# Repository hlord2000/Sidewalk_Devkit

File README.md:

# Sidewalk Devkit

KiCad hardware design for a compact Nordic Semiconductor devkit built around an
`nRF54L15` target, `nPM1300` power management, and an `SX1262` sub-GHz radio
front end.

## Hardware

- `nRF54L15-QFAA` target SoC with external `32 MHz` and `32.768 kHz` crystals.
- `nPM1300-QEAA` PMIC for USB/battery power management, charging, and status LEDs.
- `SX1262IMLTRT` sub-GHz transceiver with RF switch/filter network, U.FL, and chip antenna footprints.
- On-board `nRF52833-QDXX` debug helper with USB, SWD, UART, and level-translated target boundary.
- USB-C input with ESD protection and a 1 A fuse.
- Battery connector, reset/user buttons, and board-edge debug/test access.
- `STEMMA QT` I2C expansion connector.
- `SHT4x` humidity/temperature sensor, `ADXL367` accelerometer, and `ZD25WQ16CEIGR` QSPI flash.
- NFC connector footprint and user/status LEDs.

## Board

| Property | Value |
| --- | --- |
| KiCad version | 10.x project files |
| Board revision | `0.1` |
| Size | `55 mm x 34 mm` |
| Stackup | 6 copper layers, 1.6 mm board thickness |
| Minimum track / clearance | `0.127 mm / 0.127 mm` |
| Minimum drill | `0.200 mm` |

## Passed Qualification Tests

- Flashing the `nRF54L15` target from the on-board `nRF52833` debug helper.
- RTT logging.
- UART logging.
- BLE validation.
- NFC validation.
- Sensor and PMIC logging from `SHT40`, `ADXL367`, and `nPM1300`.
- `SX1262` radio operation in both FSK and LoRa modes.
- Sidewalk operation over all transports.

### Top

### Bottom

## Schematic Structure

The design is split into hierarchical KiCad sheets:

- `sch/nRF54L15.kicad_sch` - target SoC, sensors, QSPI flash, STEMMA QT, NFC, and user IO.
- `sch/SX1262.kicad_sch` - sub-GHz radio, RF matching/filtering, antenna switch, and RF connectors.
- `sch/nPM1300.kicad_sch` - USB-C, battery input, PMIC rails, charger support, and PMIC LEDs.
- `sch/Debugger.kicad_sch` - on-board debug helper, target SWD/UART boundary, and level shifting.

## Repository Layout

```text
.
|-- Sidewalk_Devkit.kicad_pro   KiCad project
|-- Sidewalk_Devkit.kicad_sch   Top-level schematic
|-- Sidewalk_Devkit.kicad_pcb   PCB layout
|-- sch/                        Hierarchical schematic sheets
|-- lib/                        Local symbols, footprints, and 3D models
|-- docs/images/                README render images
|-- build/                      Local generated outputs, ignored by git
`-- debug_helper_parts.md       Notes for the debug-helper boundary parts
```

## Regenerating Outputs

The README images are rendered directly from the KiCad PCB:

```bash
mkdir -p docs/images

kicad-cli pcb render Sidewalk_Devkit.kicad_pcb \
  --output docs/images/sidewalk-devkit-hero.png \
  --width 1800 --height 1000 \
  --background opaque --quality high --perspective \
  --rotate '-35,0,35' --zoom 0.84

kicad-cli pcb render Sidewalk_Devkit.kicad_pcb \
  --output docs/images/sidewalk-devkit-top.png \
  --width 1600 --height 900 \
  --side top --background opaque --quality high --zoom 1.12

kicad-cli pcb render Sidewalk_Devkit.kicad_pcb \
  --output docs/images/sidewalk-devkit-bottom.png \
  --width 1600 --height 900 \
  --side bottom --background opaque --quality high --zoom 1.12
```

Useful local exports:

```bash
mkdir -p build

kicad-cli sch export pdf Sidewalk_Devkit.kicad_sch \
  --output build/schematic.pdf

kicad-cli pcb export step Sidewalk_Devkit.kicad_pcb \
  --output build/board.step

kicad-cli sch export bom Sidewalk_Devkit.kicad_sch \
  --output build/bom.csv \
  --fields Reference,Value,Footprint,QUANTITY,DNP \
  --group-by Value,Footprint
```

The custom EasyEDA-derived footprints and 3D models live under `lib/`. STEP
export may still warn if a local KiCad installation does not include every
referenced stock KiCad 3D model.

Run design checks before fabrication or release:

```bash
mkdir -p build
kicad-cli sch erc Sidewalk_Devkit.kicad_sch --output build/erc.rpt
kicad-cli pcb drc Sidewalk_Devkit.kicad_pcb --output build/drc.rpt
```

## License

This hardware design is licensed under the CERN Open Hardware Licence Version 2
- Permissive. See [LICENSE](LICENSE).

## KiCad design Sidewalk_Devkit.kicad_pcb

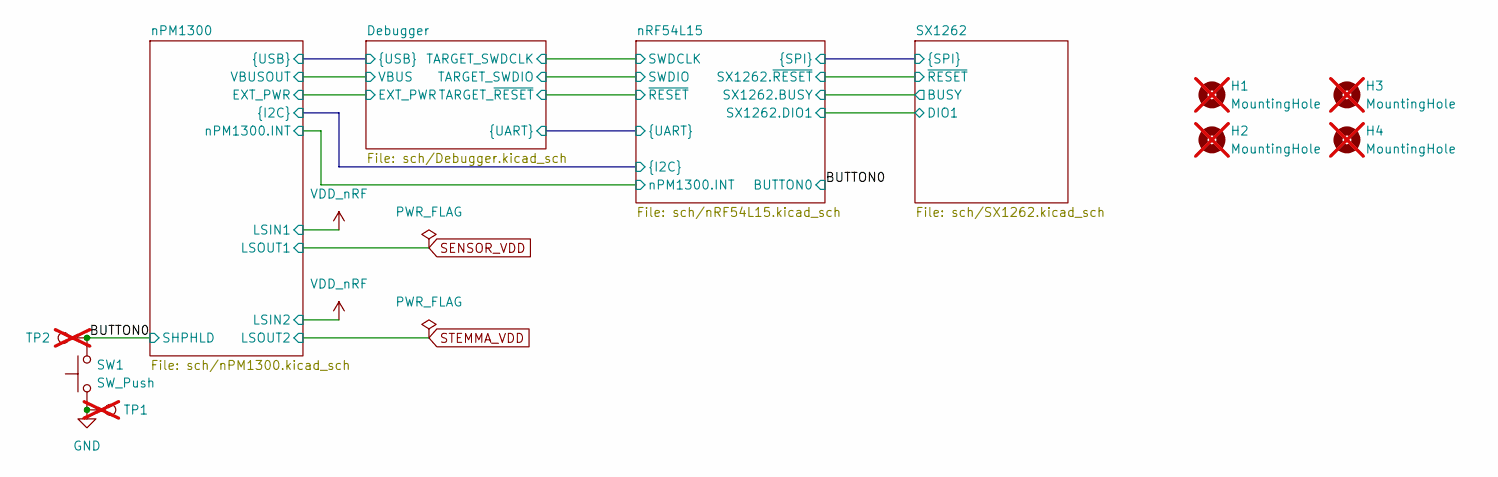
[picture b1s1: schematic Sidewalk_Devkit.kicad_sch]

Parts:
H1, H2, H3, H4: MountingHole; MountingHole_2.2mm_M2; not fitted
SW1: SW_Push; SW_Push_1P1T_NO_Vertical_Wuerth_434133025816; LCSC C127488
TP1: TestPoint; TestPoint_Keystone_5015_Micro_Mini; not fitted
TP2: TestPoint; TestPoint_Pad_D1.0mm; not fitted

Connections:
/BUTTON0: SW1.2, TP2.1 (1_1); also elsewhere on the board
GND: SW1.1, TP1.1 (1_1); also elsewhere on the board

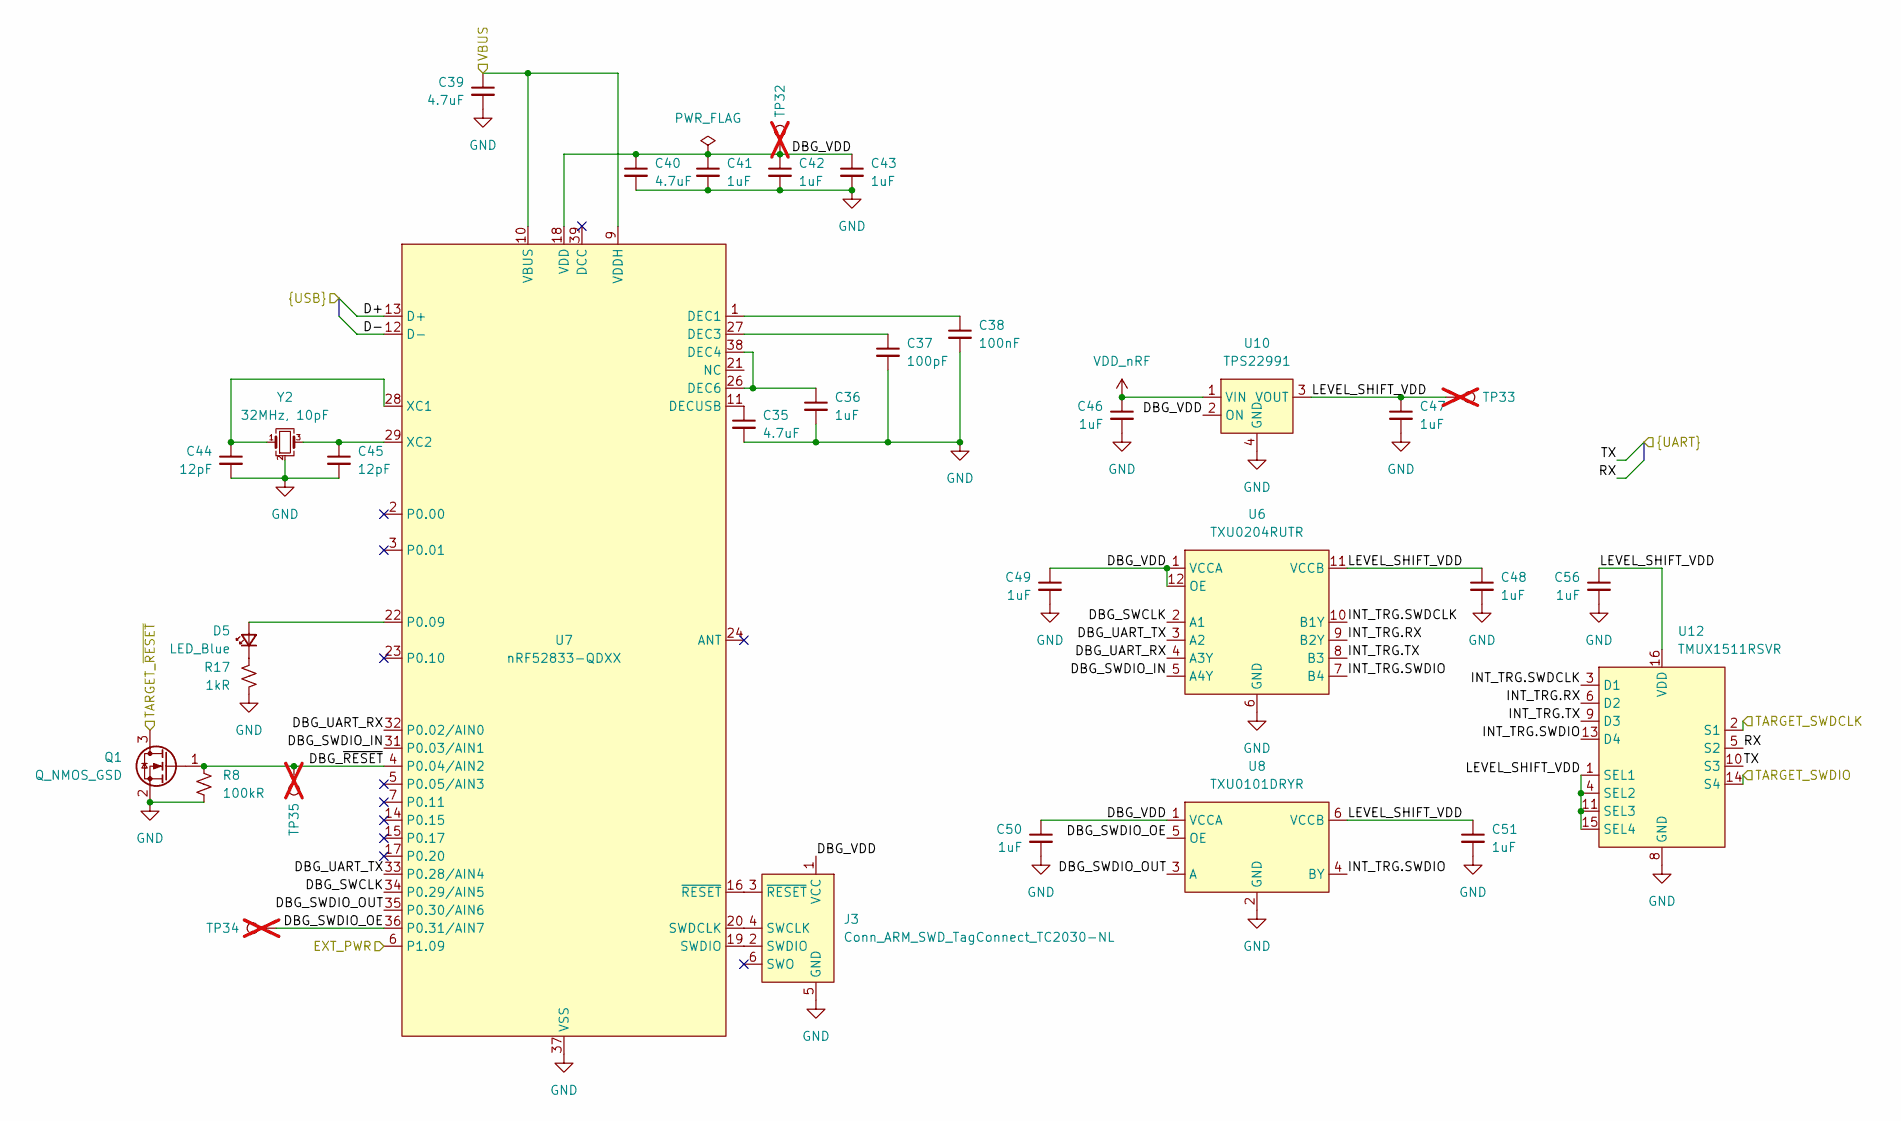
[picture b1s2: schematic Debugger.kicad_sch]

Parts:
C35, C40: 4.7uF; C_0201_0603Metric_L; LCSC C335103
C36, C41, C42, C43, C46, C47, C48, C49, C50, C51, C56: 1uF; C_0201_0603Metric_L; LCSC C76935
C37: 100pF; C_0201_0603Metric_L; LCSC C62550
C38: 100nF; C_0201_0603Metric_L; LCSC C467016
C39: 4.7uF; C_0402_1005Metric_L; LCSC C23733
C44, C45: 12pF; C_0201_0603Metric_L; LCSC C384960
D5: LED_Blue; LED_0603_1608Metric; LCSC C7496819
J3: Conn_ARM_SWD_TagConnect_TC2030-NL; Tag-Connect_TC2030-IDC-NL_2x03_P1.27mm_Vertical
Q1: Q_NMOS_GSD; Diodes_DFN1006-3; LCSC C19949844
R8: 100kR; C_0201_0603Metric_L; LCSC C106224
R17: 1kR; C_0201_0603Metric_L; LCSC C138165
TP32, TP33, TP34, TP35: TestPoint; TestPoint_Pad_D1.0mm; not fitted
U6: TXU0204RUTR; UQFN-12_L2.0-W1.7-P0.40-TL; MPN TXU0204RUTR; LCSC C5217875
U7: nRF52833-QDXX; QFN-40-1EP_5x5mm_P0.4mm_EP3.6x3.6mm_ThermalVias; LCSC C3007767
U8: TXU0101DRYR; SON-6_L1.5-W1.0-P0.50-TL; MPN TXU0101DRYR; LCSC C5217869
U10: TPS22991; 4-UQFN-0.9x0.8mm; LCSC C49307573
U12: TMUX1511RSVR; UTQFN-16_L2.6-W1.8-P0.40-BL; MPN TMUX1511RSVR; LCSC Part C2673275
Y2: 32MHz, 10pF; Crystal_SMD_2016-4Pin_2.0x1.6mm; LCSC C54427949

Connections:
/Debugger/D+: U7.13 (D+); also elsewhere on the board
/Debugger/D-: U7.12 (D-); also elsewhere on the board
/Debugger/DBG_SWCLK: U6.2 (A1), U7.34 (P0.29/AIN5)
/Debugger/DBG_SWDIO_IN: U6.5 (A4Y), U7.31 (P0.03/AIN1)
/Debugger/DBG_SWDIO_OE: TP34.1 (1_1), U7.36 (P0.31/AIN7), U8.5 (OE)
/Debugger/DBG_SWDIO_OUT: U7.35 (P0.30/AIN6), U8.3 (A)
/Debugger/DBG_UART_RX: U6.4 (A3Y), U7.32 (P0.02/AIN0)
/Debugger/DBG_UART_TX: U6.3 (A2), U7.33 (P0.28/AIN4)
/Debugger/DBG_VDD: C40.1, C41.1, C42.1, C43.1, C49.1, C50.1, J3.1 (VCC), TP32.1 (1_1), U6.1 (VCCA), U6.12 (OE), U7.8 (VDD), U7.18 (VDD), U7.30 (VDD), U7.40 (VDD), U8.1 (VCCA), U10.2 (ON)
/Debugger/DBG_~RESET: Q1.1 (G), R8.1, TP35.1 (1_1), U7.4 (P0.04/AIN2)
/Debugger/EXT_PWR: U7.6 (P1.09); also elsewhere on the board
/Debugger/INT_TRG.RX: U6.9 (B2Y), U12.6 (D2)
/Debugger/INT_TRG.SWDCLK: U6.10 (B1Y), U12.3 (D1)
/Debugger/INT_TRG.SWDIO: U6.7 (B4), U8.4 (BY), U12.13 (D4)
/Debugger/INT_TRG.TX: U6.8 (B3), U12.9 (D3)
/Debugger/LEVEL_SHIFT_VDD: C47.1, C48.1, C51.1, C56.1, TP33.1 (1_1), U6.11 (VCCB), U8.6 (VCCB), U10.3 (VOUT), U12.1 (SEL1), U12.4 (SEL2), U12.11 (SEL3), U12.15 (SEL4), U12.16 (VDD)
/Debugger/RX: U12.5 (S2); also elsewhere on the board
/Debugger/TARGET_SWDCLK: U12.2 (S1); also elsewhere on the board
/Debugger/TARGET_SWDIO: U12.14 (S4); also elsewhere on the board
/Debugger/TARGET_~RESET: Q1.3 (D); also elsewhere on the board
/Debugger/TX: U12.10 (S3); also elsewhere on the board
/Debugger/VBUS: C39.1, U7.9 (VDDH), U7.10 (VBUS); also elsewhere on the board
GND: C35.2, C36.2, C37.2, C38.2, C39.2, C40.2, C41.2, C42.2, C43.2, C44.2, C45.2, C46.2, C47.2, C48.2, C49.2, C50.2, C51.2, C56.2, J3.5 (GND), Q1.2 (S), R8.2, R17.2, U6.6 (GND), U7.25 (VSS_PA), U7.37 (VSS), U7.41 (VSS), U8.2 (GND), U10.4 (GND), U12.8 (GND), Y2.2 (G), Y2.4 (G); also elsewhere on the board
unnamed: D5.2 (A), U7.22 (P0.09)
unnamed: D5.1 (K), R17.1
unnamed: J3.4 (SWCLK), U7.20 (SWDCLK)
unnamed: J3.2 (SWDIO), U7.19 (SWDIO)
unnamed: J3.3 (~RESET), U7.16 (~RESET)
unnamed: C38.1, U7.1 (DEC1)
unnamed: C37.1, U7.27 (DEC3)
unnamed: C36.1, U7.26 (DEC6), U7.38 (DEC4)
unnamed: C35.1, U7.11 (DECUSB)
unnamed: C44.1, U7.28 (XC1), Y2.1
unnamed: C45.1, U7.29 (XC2), Y2.3
VDD_nRF: C46.1, U10.1 (VIN); also elsewhere on the board

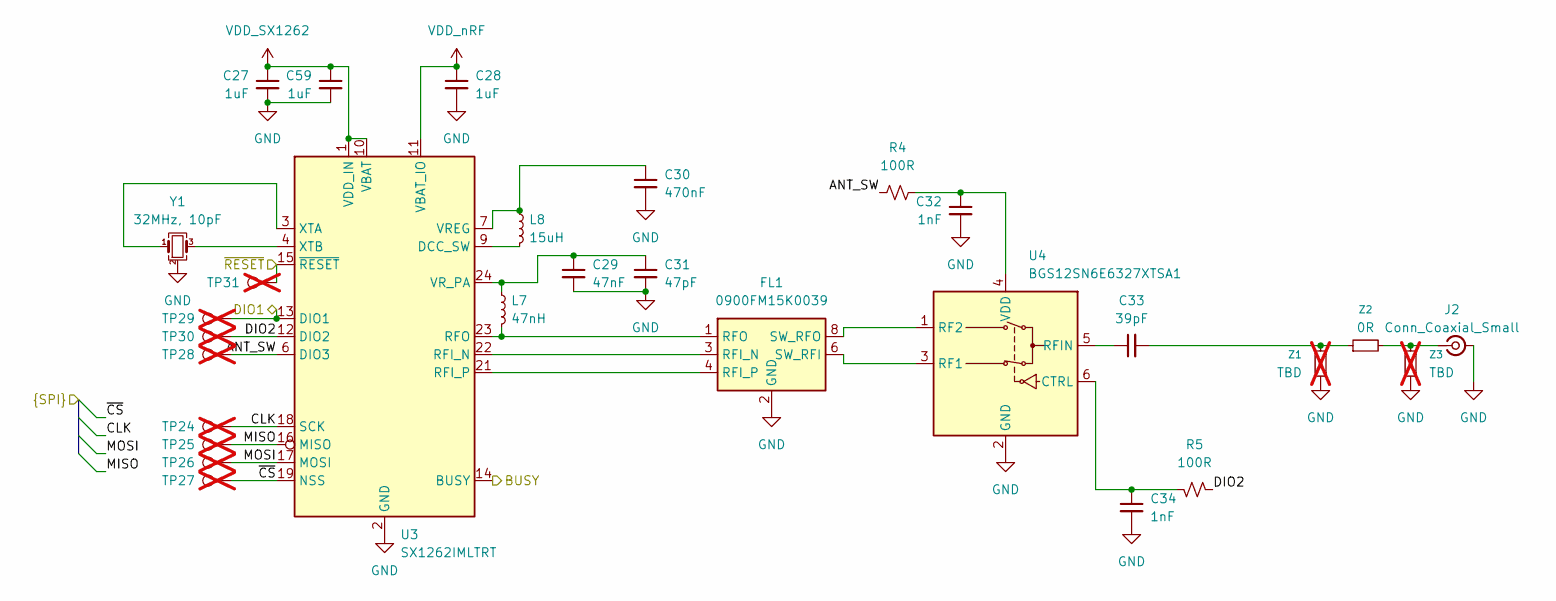
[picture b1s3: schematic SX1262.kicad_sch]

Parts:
C27, C28, C59: 1uF; C_0201_0603Metric_L; LCSC C76935
C29: 47nF; C_0201_0603Metric_L; LCSC C88917
C30: 470nF; C_0201_0603Metric_L; LCSC C85926
C31: 47pF; C_0201_0603Metric_L; LCSC C62546
C32, C34: 1nF; C_0201_0603Metric_L; LCSC C66942
C33: 39pF; C_0201_0603Metric_L; LCSC C85904
FL1: 0900FM15K0039; Balun_Johanson_0900FM15K0039; LCSC C7434807
J2: Conn_Coaxial_Small; U.FL_Hirose_U.FL-R-SMT-1_Vertical; LCSC C88374
L7: 47nH; L_0201_0603Metric_L; LCSC C1857885
L8: 15uH; L_0603_1608Metric_L; LCSC C2838019
R4, R5: 100R; C_0201_0603Metric_L; LCSC C77623
TP24, TP25, TP26, TP27, TP28, TP29, TP30, TP31: TestPoint; TestPoint_Pad_D1.0mm; not fitted
U3: SX1262IMLTRT; QFN-24-1EP_4x4mm_P0.5mm_EP2.6x2.6mm_ThermalVias; LCSC C191341
U4: BGS12SN6E6327XTSA1; Infineon_PG-TSNP-6-10_0.7x1.1mm_0.7x1.1mm_P0.4mm; LCSC C114953
Y1: 32MHz, 10pF; Crystal_SMD_2016-4Pin_2.0x1.6mm; LCSC C1986260
Z1, Z3: TBD; C_0201_0603Metric_L; not fitted
Z2: 0R; C_0201_0603Metric_L; LCSC C473473

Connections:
/SX1262/ANT_SW: R4.1, TP28.1 (1_1), U3.6 (DIO3)
/SX1262/BUSY: U3.14 (BUSY); also elsewhere on the board
/SX1262/CLK: TP24.1 (1_1), U3.18 (SCK); also elsewhere on the board
/SX1262/DIO1: TP29.1 (1_1), U3.13 (DIO1); also elsewhere on the board
/SX1262/DIO2: R5.1, TP30.1 (1_1), U3.12 (DIO2)
/SX1262/MISO: TP25.1 (1_1), U3.16 (MISO); also elsewhere on the board
/SX1262/MOSI: TP26.1 (1_1), U3.17 (MOSI); also elsewhere on the board
/SX1262/~CS: TP27.1 (1_1), U3.19 (NSS); also elsewhere on the board
/SX1262/~RESET: TP31.1 (1_1), U3.15 (~RESET); also elsewhere on the board
GND: C27.2, C28.2, C29.2, C30.2, C31.2, C32.2, C34.2, C59.2, FL1.2 (GND), FL1.5 (GND), FL1.7 (GND), FL1.9 (GND), FL1.10 (GND), J2.2 (Ext), U3.2 (GND), U3.5 (GND), U3.8 (GND), U3.20 (GND), U3.25 (GND), U4.2 (GND), Y1.2 (G), Y1.4 (G), Z1.1, Z3.1; also elsewhere on the board
unnamed: C33.2, Z1.2, Z2.1
unnamed: FL1.3 (RFI_N), U3.22 (RFI_N)
unnamed: FL1.4 (RFI_P), U3.21 (RFI_P)
unnamed: FL1.1 (RFO), L7.2, U3.23 (RFO)
unnamed: FL1.6 (SW_RFI), U4.3 (RF1)
unnamed: FL1.8 (SW_RFO), U4.1 (RF2)
unnamed: J2.1 (In), Z2.2, Z3.2
unnamed: L8.2, U3.9 (DCC_SW)
unnamed: C30.1, L8.1, U3.7 (VREG)
unnamed: C29.1, C31.1, L7.1, U3.24 (VR_PA)
unnamed: U3.3 (XTA), Y1.1
unnamed: U3.4 (XTB), Y1.3
unnamed: C34.1, R5.2, U4.6 (CTRL)
unnamed: C33.1, U4.5 (RFIN)
unnamed: C32.1, R4.2, U4.4 (VDD)
VDD_SX1262: C27.1, C59.1, U3.1 (VDD_IN), U3.10 (VBAT); also elsewhere on the board
VDD_nRF: C28.1, U3.11 (VBAT_IO); also elsewhere on the board

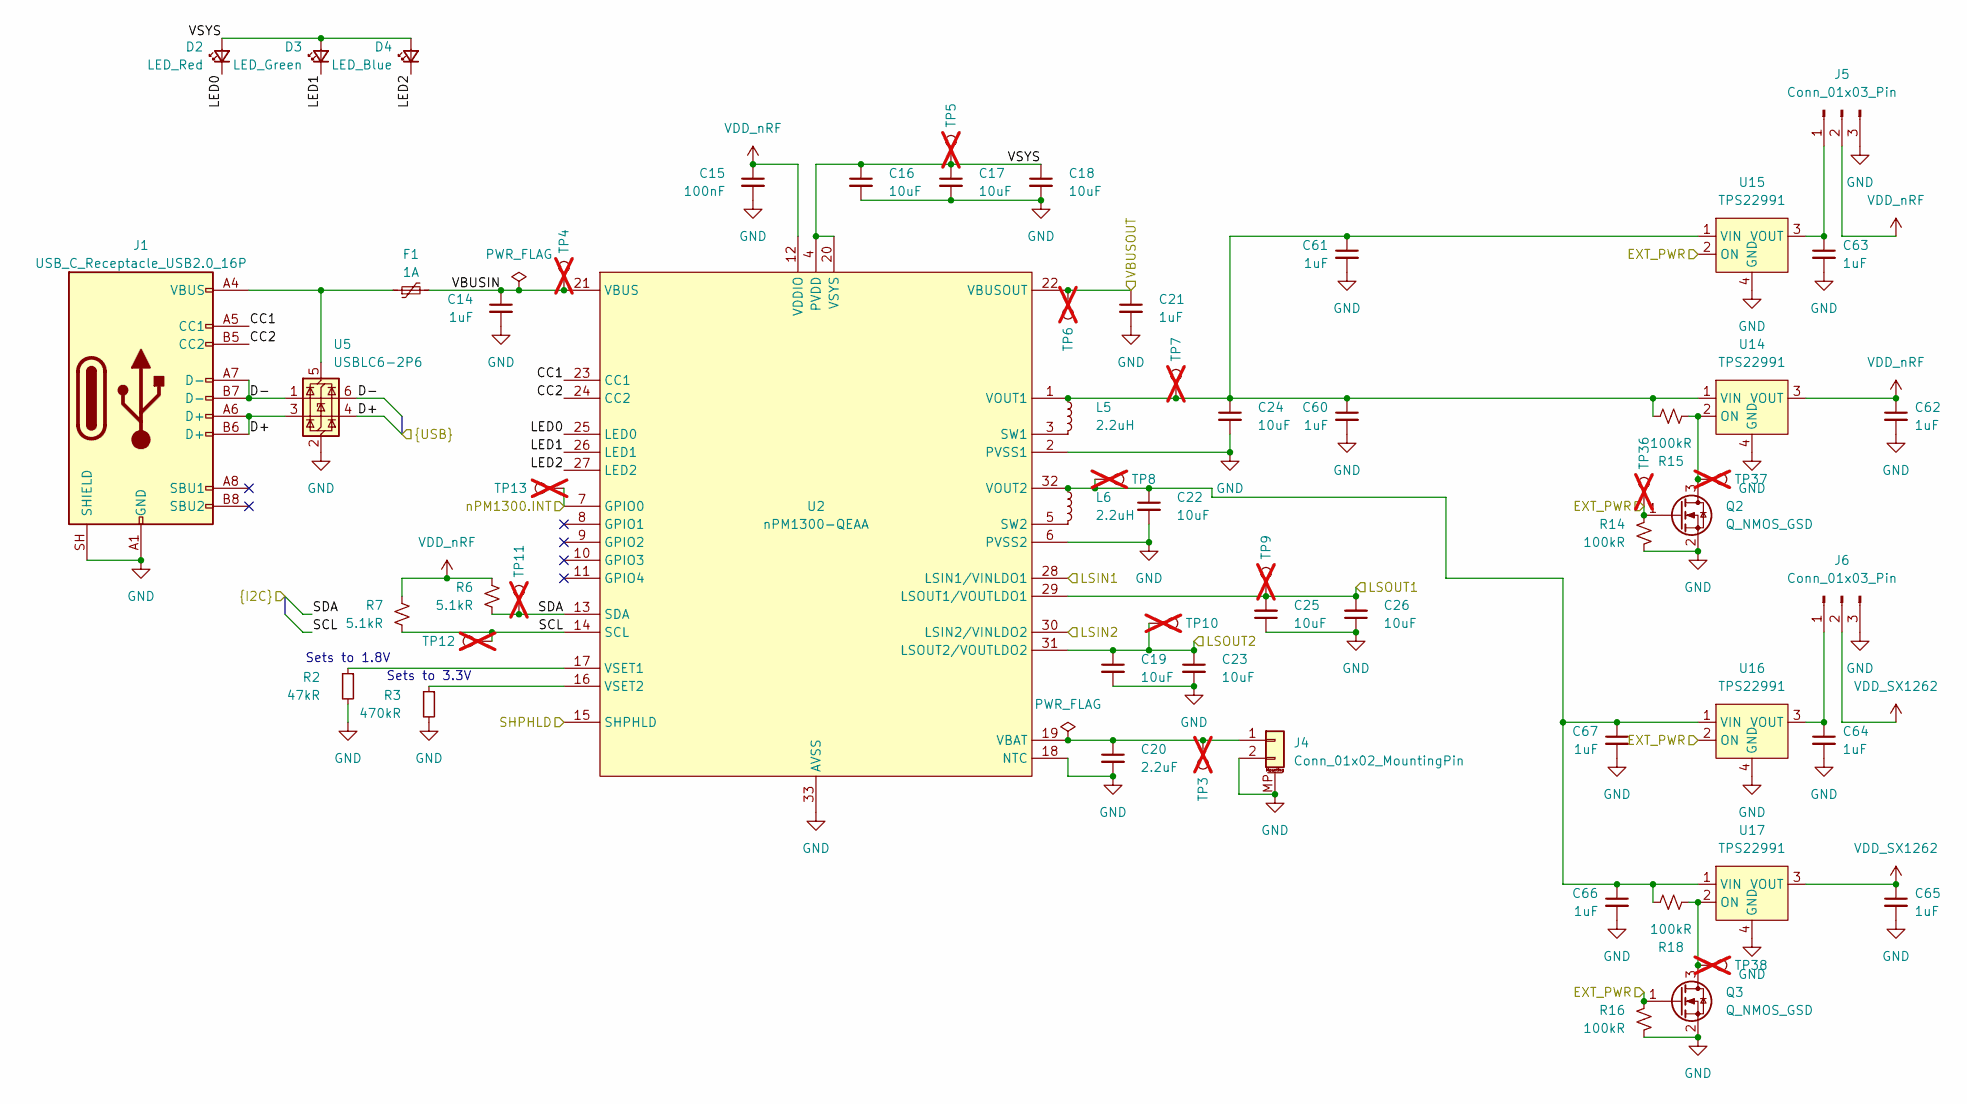
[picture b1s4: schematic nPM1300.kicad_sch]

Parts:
C14, C21: 1uF; C_0603_1608Metric_L; LCSC C15849
C15: 100nF; C_0201_0603Metric_L; LCSC C467016
C16, C17, C18, C19, C22, C23, C24, C25, C26: 10uF; C_0603_1608Metric_L; LCSC C19702
C20: 2.2uF; C_0603_1608Metric_L; LCSC C23630
C60, C61, C62, C63, C64, C65, C66, C67: 1uF; C_0201_0603Metric_L; LCSC C76935
D2: LED_Red; LED_0603_1608Metric; LCSC C2286
D3: LED_Green; LED_0603_1608Metric; LCSC C19189745
D4: LED_Blue; LED_0603_1608Metric; LCSC C965807
F1: 1A; Fuse_0603_1608Metric; LCSC C516069
J1: USB_C_Receptacle_USB2.0_16P; USB_C_Receptacle_HRO_TYPE-C-31-M-12-Edge_Silkscreen_Removed; LCSC C165948
J4: Conn_01x02_MountingPin; JST_ACH_BM02B-ACHSS-GAN-ETF_1x02-1MP_P1.20mm_Vertical; LCSC C5118738
J5, J6: Conn_01x03_Pin; PinHeader_1x03_P2.54mm_Vertical
L5, L6: 2.2uH; L_0806_2016Metric_L; LCSC C412023
Q2, Q3: Q_NMOS_GSD; Diodes_DFN1006-3; LCSC C19949844
R2: 47kR; R_0201_0603Metric_L; LCSC C138139
R3: 470kR; R_0201_0603Metric_L; LCSC C274343
R6, R7: 5.1kR; C_0201_0603Metric_L; LCSC C270344
R14, R15, R16, R18: 100kR; C_0201_0603Metric_L; LCSC C106224
TP3, TP4, TP5, TP6, TP7, TP8, TP9, TP10, TP11, TP12, TP13, TP36, TP37, TP38: TestPoint; TestPoint_Pad_D1.0mm; not fitted
U2: nPM1300-QEAA; QFN-32-1EP_5x5mm_P0.5mm_EP3.6x3.6mm_ThermalVias; LCSC C30627544
U5: USBLC6-2P6; SOT-666; LCSC C15999
U14, U15, U16, U17: TPS22991; 4-UQFN-0.9x0.8mm; LCSC C49307573

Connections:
/BUTTON0: U2.15 (SHPHLD); also elsewhere on the board
/Debugger/D+: J1.A6 (D+), J1.B6 (D+), U5.3 (I/O2), U5.4 (I/O2); also elsewhere on the board
/Debugger/D-: J1.A7 (D-), J1.B7 (D-), U5.1 (I/O1), U5.6 (I/O1); also elsewhere on the board
/Debugger/EXT_PWR: Q2.1 (G), Q3.1 (G), R14.1, R16.1, TP36.1 (1_1), U15.2 (ON), U16.2 (ON); also elsewhere on the board
/Debugger/VBUS: C21.1, TP6.1 (1_1), U2.22 (VBUSOUT); also elsewhere on the board
/nPM1300/CC1: J1.A5 (CC1), U2.23 (CC1)
/nPM1300/CC2: J1.B5 (CC2), U2.24 (CC2)
/nPM1300/LED0: D2.1 (K), U2.25 (LED0)
/nPM1300/LED1: D3.1 (K), U2.26 (LED1)
/nPM1300/LED2: D4.1 (K), U2.27 (LED2)
/nPM1300/SCL: R7.2, TP12.1 (1_1), U2.14 (SCL); also elsewhere on the board
/nPM1300/SDA: R6.2, TP11.1 (1_1), U2.13 (SDA); also elsewhere on the board
/nPM1300/VBUSIN: C14.1, F1.2, TP4.1 (1_1), U2.21 (VBUS)
/nPM1300/VSYS: C16.1, C17.1, C18.1, D2.2 (A), D3.2 (A), D4.2 (A), TP5.1 (1_1), U2.4 (PVDD), U2.20 (VSYS)
/nPM1300/nPM1300.INT: TP13.1 (1_1), U2.7 (GPIO0); also elsewhere on the board
GND: C14.2, C15.2, C16.2, C17.2, C18.2, C19.2, C20.2, C21.2, C22.2, C23.2, C24.2, C25.1, C26.1, C60.2, C61.2, C62.2, C63.2, C64.2, C65.2, C66.2, C67.2, J1.A1 (GND), J1.A12 (GND), J1.B1 (GND), J1.B12 (GND), J1.SH (SHIELD), J4.2, J4.MP (MountPin), J5.3, J6.3, Q2.2 (S), Q3.2 (S), R2.2, R3.2, R14.2, R16.2, U2.2 (PVSS1), U2.6 (PVSS2), U2.18 (NTC), U2.33 (AVSS), U5.2 (GND), U14.4 (GND), U15.4 (GND), U16.4 (GND), U17.4 (GND); also elsewhere on the board
unnamed: C20.1, J4.1, TP3.1 (1_1), U2.19 (VBAT)
unnamed: C63.1, J5.1, U15.3 (VOUT)
unnamed: C64.1, J6.1, U16.3 (VOUT)
unnamed: Q2.3 (D), R15.2, TP37.1 (1_1), U14.2 (ON)
unnamed: Q3.3 (D), R18.2, TP38.1 (1_1), U17.2 (ON)
unnamed: L5.2, U2.3 (SW1)
unnamed: L6.1, U2.5 (SW2)
unnamed: R2.1, U2.17 (VSET1)
unnamed: R3.1, U2.16 (VSET2)
unnamed: F1.1, J1.A4 (VBUS), J1.A9 (VBUS), J1.B4 (VBUS), J1.B9 (VBUS), U5.5 (VBUS)
unnamed: C24.1, C60.1, C61.1, L5.1, R15.1, TP7.1 (1_1), U2.1 (VOUT1), U14.1 (VIN), U15.1 (VIN)
unnamed: C22.1, C66.1, C67.1, L6.2, R18.1, TP8.1 (1_1), U2.32 (VOUT2), U16.1 (VIN), U17.1 (VIN)
SENSOR_VDD: C25.2, C26.2, TP9.1 (1_1), U2.29 (LSOUT1/VOUTLDO1); also elsewhere on the board
STEMMA_VDD: C19.1, C23.1, TP10.1 (1_1), U2.31 (LSOUT2/VOUTLDO2); also elsewhere on the board
VDD_SX1262: C65.1, J6.2, U17.3 (VOUT); also elsewhere on the board
VDD_nRF: C15.1, C62.1, J5.2, R6.1, R7.1, U2.12 (VDDIO), U2.28 (LSIN1/VINLDO1), U2.30 (LSIN2/VINLDO2), U14.3 (VOUT); also elsewhere on the board

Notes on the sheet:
Sets to 1.8V
Sets to 3.3V

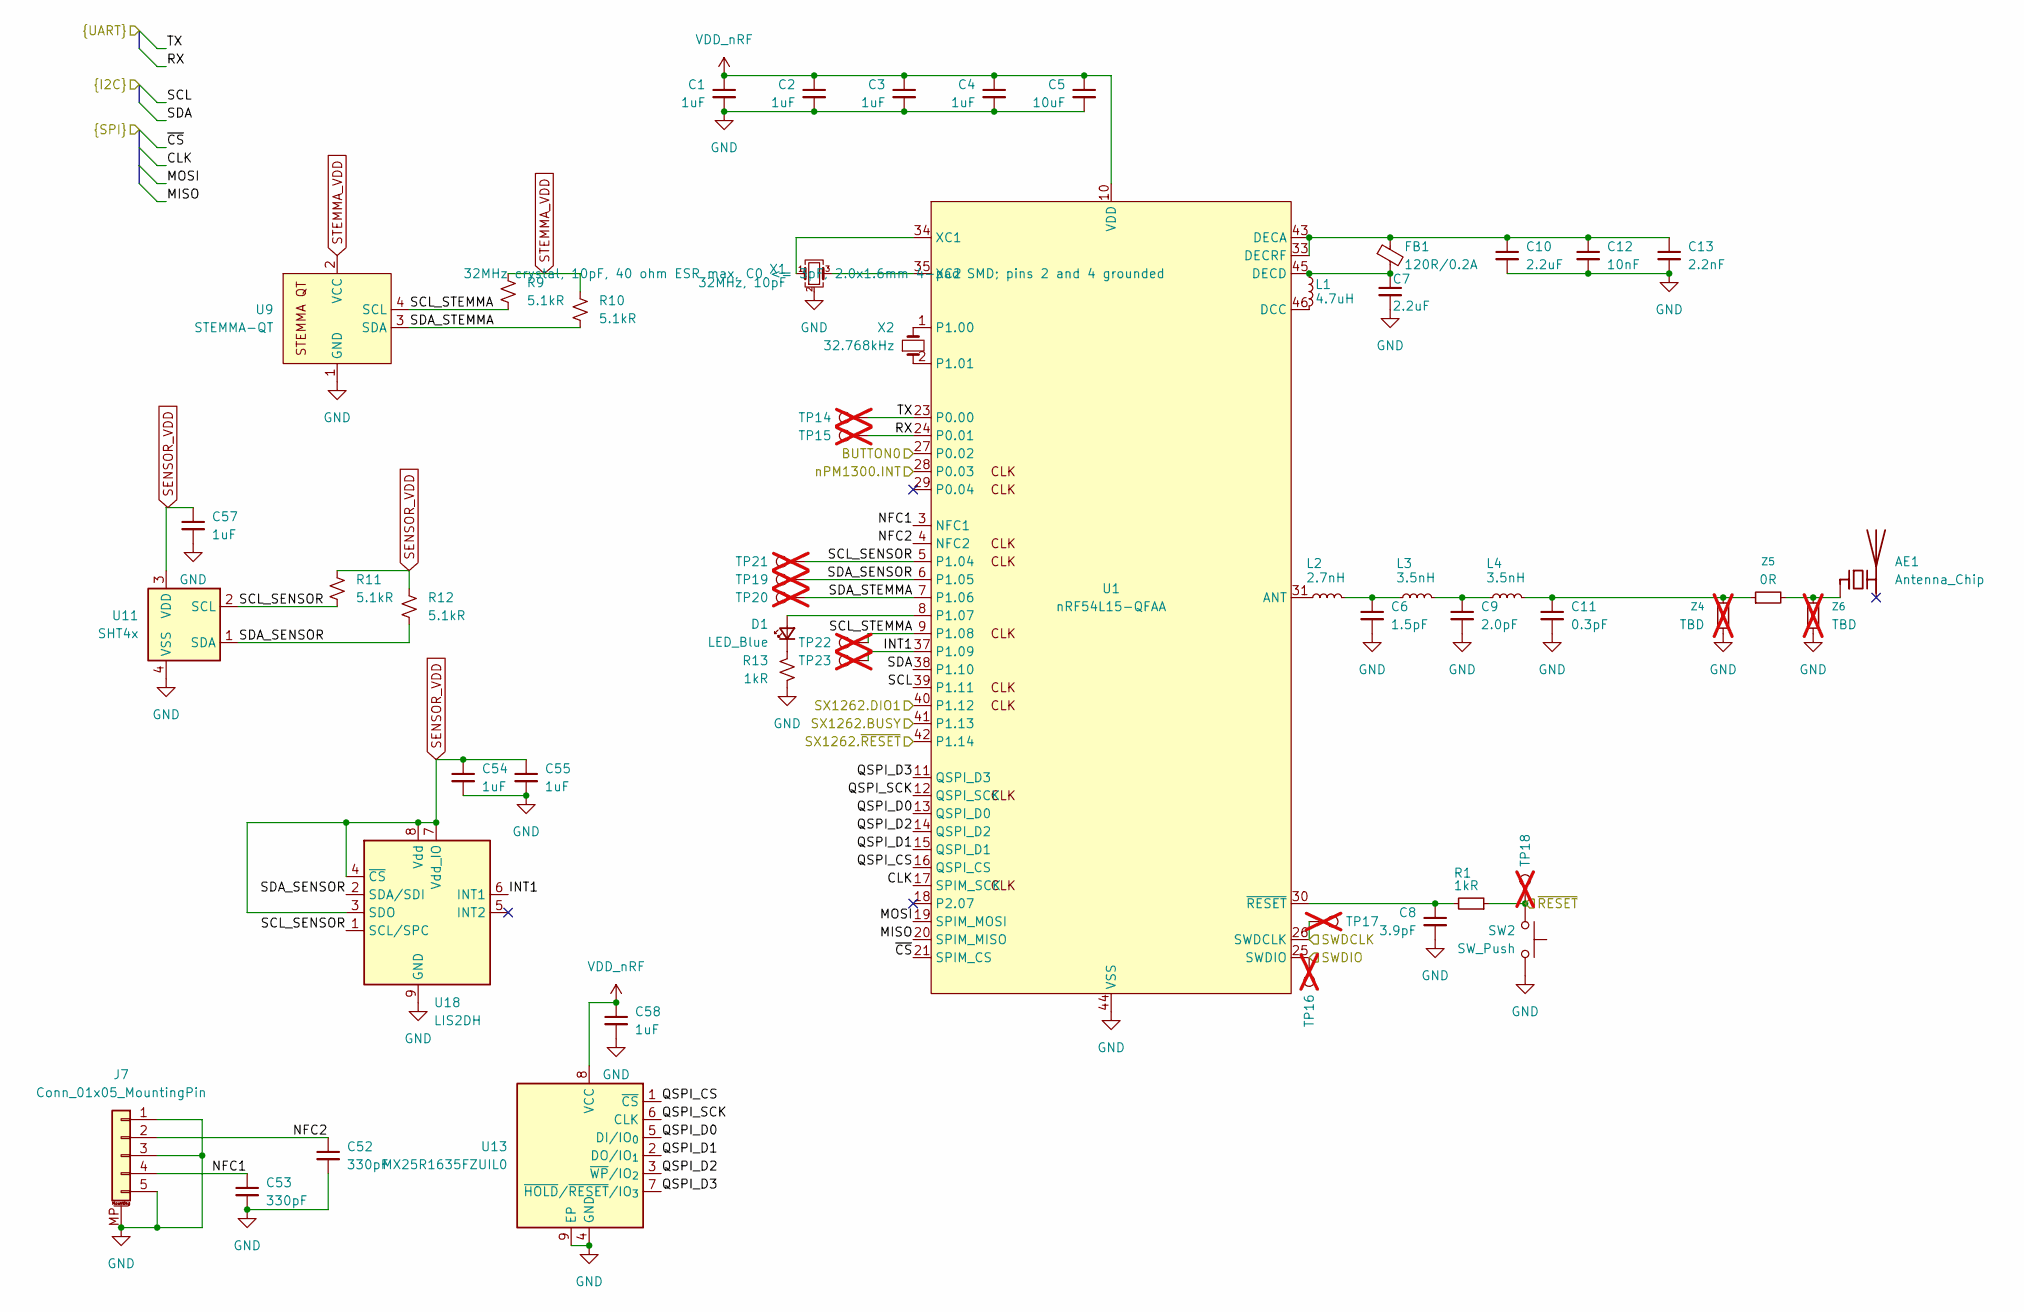
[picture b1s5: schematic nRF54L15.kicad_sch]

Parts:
AE1: Antenna_Chip; Johanson_2450AT18x100; LCSC C89334
C1, C2, C3, C4, C54, C55, C57, C58: 1uF; C_0201_0603Metric_L; LCSC C76935
C5: 10uF; C_0402_1005Metric_L; LCSC C15525
C6: 1.5pF; C_0201_0603Metric_L; LCSC C161414
C7, C10: 2.2uF; C_0201_0603Metric_L; LCSC C319184
C8: 3.9pF; C_0201_0603Metric_L; LCSC C76926
C9: 2.0pF; C_0201_0603Metric_L; LCSC C161419
C11: 0.3pF; C_0201_0603Metric_L; LCSC C161289
C12: 10nF; C_0201_0603Metric_L; LCSC C5142551
C13: 2.2nF; C_0201_0603Metric_L; LCSC C80433
C52, C53: 330pF; C_0201_0603Metric_L; LCSC C237559
D1: LED_Blue; LED_0603_1608Metric; LCSC C7496819
FB1: 120R/0.2A; L_0201_0603Metric_L; LCSC C97850
J7: Conn_01x05_MountingPin; CONN-SMD_5P-P0.50_0.5K-1.2W-5PWB; LCSC C5337029
L1: 4.7uH; L_0603_1608Metric_L; LCSC C48944999
L2: 2.7nH; L_0201_0603Metric_L; LCSC C7216765
L3, L4: 3.5nH; L_0201_0603Metric_L; LCSC C3911055
R1: 1kR; R_0201_0603Metric_L; LCSC C138165
R9, R10, R11, R12: 5.1kR; C_0201_0603Metric_L; LCSC C270344
R13: 1kR; C_0201_0603Metric_L; LCSC C138165
SW2: SW_Push; SW_Push_1P1T_NO_Vertical_Wuerth_434133025816; LCSC C127488
TP14, TP15, TP16, TP17, TP18, TP19, TP20, TP21, TP22, TP23: TestPoint; TestPoint_Pad_D1.0mm; not fitted
U1: nRF54L15-QFAA; QFN-48-1EP_6x6mm_P0.4mm_EP4.6x4.6mm_ThermalVias; LCSC C42458750
U9: STEMMA-QT; JST_SH_SM04B-SRSS-TB_1x04-1MP_P1.00mm_Horizontal; LCSC C160404
U11: SHT4x; Sensirion_DFN-4_1.5x1.5mm_P0.8mm_SHT4x_NoCentralPad; LCSC C2848306
U13: MX25R1635FZUIL0; Winbond_USON-8-1EP_3x2mm_P0.5mm_EP0.2x1.6mm; LCSC C152595
U18: LIS2DH; LGA-14_2x2mm_P0.35mm_LayoutBorder3x4y; LCSC C110926
X1: 32MHz, 10pF; Crystal_SMD_2016-4Pin_2.0x1.6mm; LCSC C54427949
X2: 32.768kHz; Crystal_SMD_2012-2Pin_2.0x1.2mm; LCSC C99009
Z4, Z6: TBD; C_0201_0603Metric_L; not fitted
Z5: 0R; C_0201_0603Metric_L; LCSC C473473

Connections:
/BUTTON0: U1.27 (P0.02); also elsewhere on the board
/Debugger/RX: TP15.1 (1_1), U1.24 (P0.01); also elsewhere on the board
/Debugger/TARGET_SWDCLK: TP17.1 (1_1), U1.26 (SWDCLK); also elsewhere on the board
/Debugger/TARGET_SWDIO: TP16.1 (1_1), U1.25 (SWDIO); also elsewhere on the board
/Debugger/TARGET_~RESET: R1.1, SW2.2, TP18.1 (1_1); also elsewhere on the board
/Debugger/TX: TP14.1 (1_1), U1.23 (P0.00); also elsewhere on the board
/SX1262/BUSY: U1.41 (P1.13); also elsewhere on the board
/SX1262/CLK: U1.17 (SPIM_SCK); also elsewhere on the board
/SX1262/DIO1: U1.40 (P1.12); also elsewhere on the board
/SX1262/MISO: U1.20 (SPIM_MISO); also elsewhere on the board
/SX1262/MOSI: U1.19 (SPIM_MOSI); also elsewhere on the board
/SX1262/~CS: U1.21 (SPIM_CS); also elsewhere on the board
/SX1262/~RESET: U1.42 (P1.14); also elsewhere on the board
/nPM1300/SCL: U1.39 (P1.11); also elsewhere on the board
/nPM1300/SDA: U1.38 (P1.10); also elsewhere on the board
/nPM1300/nPM1300.INT: U1.28 (P0.03); also elsewhere on the board
/nRF54L15/INT1: TP23.1 (1_1), U1.37 (P1.09), U18.6 (INT1)
/nRF54L15/NFC1: C53.1, J7.4, U1.3 (NFC1)
/nRF54L15/NFC2: C52.1, J7.2, U1.4 (NFC2)
/nRF54L15/QSPI_CS: U1.16 (QSPI_CS), U13.1 (~CS)
/nRF54L15/QSPI_D0: U1.13 (QSPI_D0), U13.5 (DI/IO_{0})
/nRF54L15/QSPI_D1: U1.15 (QSPI_D1), U13.2 (DO/IO_{1})
/nRF54L15/QSPI_D2: U1.14 (QSPI_D2), U13.3 (~WP/IO_{2})
/nRF54L15/QSPI_D3: U1.11 (QSPI_D3), U13.7 (~HOLD/~RESET/IO_{3})
/nRF54L15/QSPI_SCK: U1.12 (QSPI_SCK), U13.6 (CLK)
/nRF54L15/SCL_SENSOR: R11.2, TP21.1 (1_1), U1.5 (P1.04), U11.2 (SCL), U18.1 (SCL/SPC)
/nRF54L15/SCL_STEMMA: R9.2, TP22.1 (1_1), U1.9 (P1.08), U9.4 (SCL)
/nRF54L15/SDA_SENSOR: R12.2, TP19.1 (1_1), U1.6 (P1.05), U11.1 (SDA), U18.2 (SDA/SDI)
/nRF54L15/SDA_STEMMA: R10.2, TP20.1 (1_1), U1.7 (P1.06), U9.3 (SDA)
GND: C1.2, C2.2, C3.2, C4.2, C5.2, C6.2, C7.2, C8.2, C9.2, C10.2, C11.2, C12.2, C13.2, C52.2, C53.2, C54.2, C55.2, C57.2, C58.2, J7.1, J7.3, J7.5, J7.MP (MountPin), R13.2, SW2.1, U1.32 (VSS_PA), U1.44 (VSS), U1.49 (VSS), U9.1 (GND), U9.MP (GND), U11.4 (VSS), U13.4 (GND), U13.9 (EP), U18.9 (GND), U18.10 (GND), U18.11 (GND), U18.12 (GND), U18.13 (GND), U18.14 (GND), X1.2 (G), X1.4 (G), Z4.1, Z6.1; also elsewhere on the board
unnamed: AE1.1 (FEED_1), Z5.2, Z6.2
unnamed: C6.1, L2.2, L3.1
unnamed: C9.1, L3.2, L4.1
unnamed: C11.1, L4.2, Z4.2, Z5.1
unnamed: D1.2 (A), U1.8 (P1.07)
unnamed: D1.1 (K), R13.1
unnamed: L2.1, U1.31 (ANT)
unnamed: L1.2, U1.46 (DCC)
unnamed: C10.1, C12.1, C13.1, FB1.1, U1.33 (DECRF), U1.43 (DECA)
unnamed: C7.1, FB1.2, L1.1, U1.45 (DECD)
unnamed: U1.1 (P1.00), X2.2
unnamed: U1.2 (P1.01), X2.1
unnamed: U1.34 (XC1), X1.1
unnamed: U1.35 (XC2), X1.3
unnamed: C8.1, R1.2, U1.30 (~RESET)
SENSOR_VDD: C54.1, C55.1, C57.1, R11.1, R12.1, U11.3 (VDD), U18.3 (SDO), U18.4 (~CS), U18.7 (Vdd_IO), U18.8 (Vdd); also elsewhere on the board
STEMMA_VDD: R9.1, R10.1, U9.2 (VCC); also elsewhere on the board
VDD_nRF: C1.1, C2.1, C3.1, C4.1, C5.1, C58.1, U1.10 (VDD), U1.22 (VDD), U1.36 (VDD), U1.47 (VDD), U1.48 (VDD), U13.8 (VCC); also elsewhere on the board

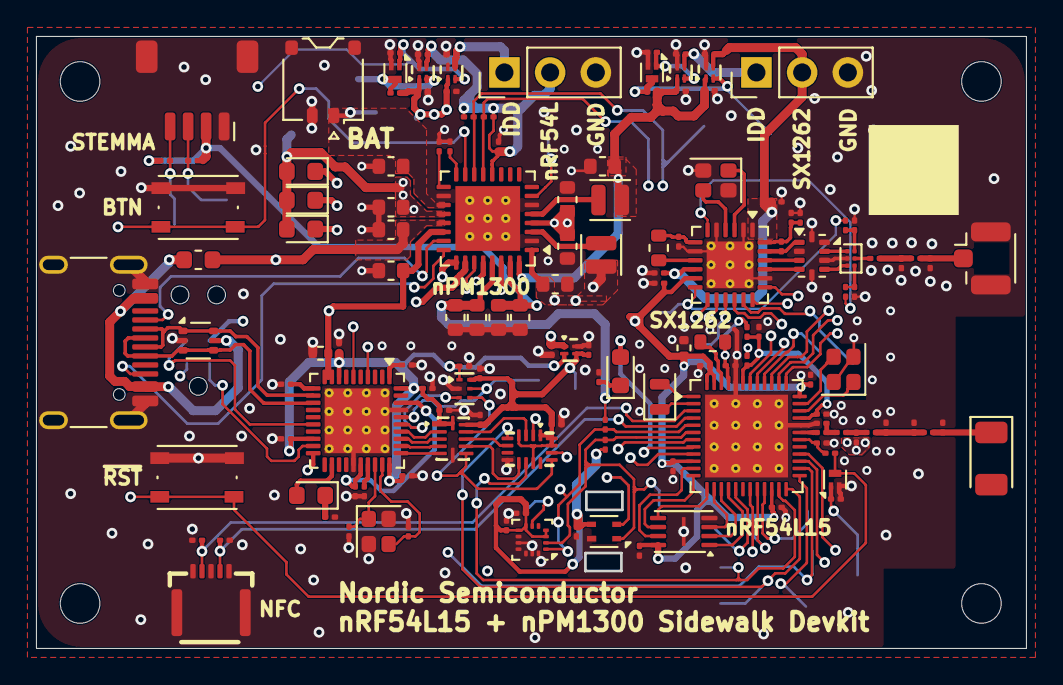
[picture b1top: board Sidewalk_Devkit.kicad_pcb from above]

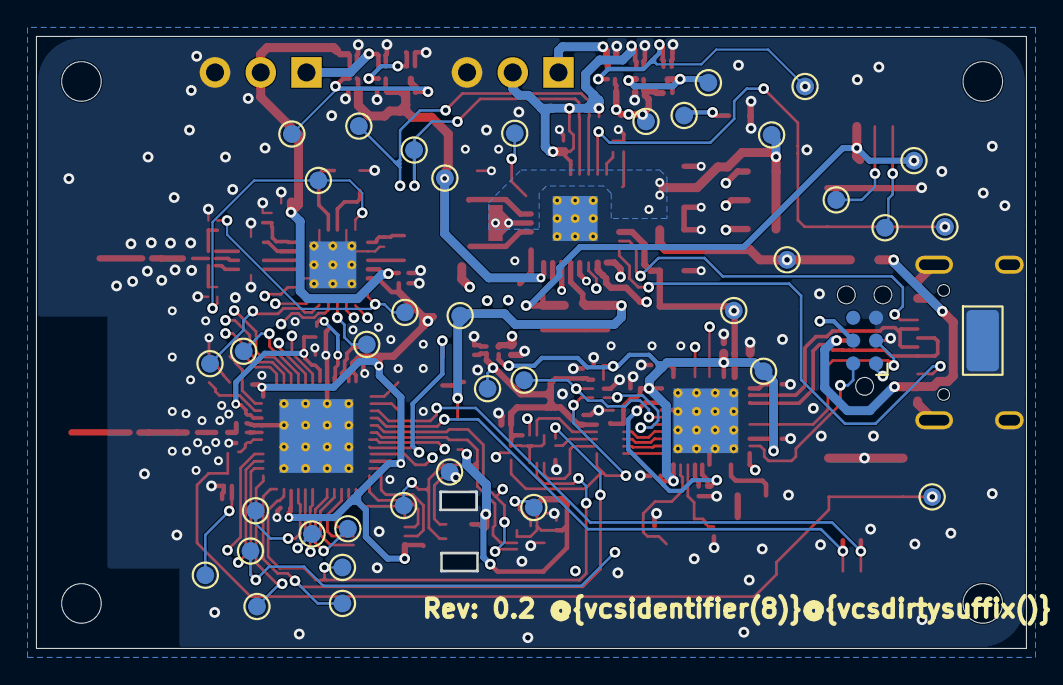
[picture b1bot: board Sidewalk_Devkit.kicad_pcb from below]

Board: 6 copper layers, 54.9 x 33.9 mm, 184 parts (39 on the bottom side), 113 nets.

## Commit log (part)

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2026-06-02 Initial commit.
2026-06-02 Updates for rev 1
2026-06-16 Add README
2026-06-16 Add missing 3D models
2026-06-16 Add board PDFs
2026-06-16 Added passing tests
2026-06-18 Added external current measurement for L15 and SX1262
